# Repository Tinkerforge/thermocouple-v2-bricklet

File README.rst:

Thermocouple Bricklet 2.0
=========================

This repository contains the firmware source code and the hardware design
files. The documentation generator configs can be found at
https://github.com/Tinkerforge/generators

Repository Content
------------------

software/:
 * examples/: Examples for all supported languages
 * build/: Compiled files
 * src/: Source code of firmware
 * Makefile: Makefile to build project

hardware/:
 * Contains KiCad project files and additionally schematics as PDF

datasheets/:
 * Contains datasheets for sensors and complex ICs that are used

Hardware
--------

The hardware is designed with the open source EDA Suite KiCad
(http://www.kicad.org). Before you are able to open the files,
you have to install the Tinkerforge kicad-libraries
(https://github.com/Tinkerforge/kicad-libraries). You can either clone
them directly in hardware/ or clone them in a separate folder and
symlink them into hardware/
(ln -s kicad_path/kicad-libraries project_path/hardware). After that you
can open the .pro file in hardware/ with KiCad and from there view and
modify the schematics and the PCB layout.

Software
--------

If you want to do your own Brick/Bricklet firmware development we highly
recommend that you use our build environment setup script and read the
tutorial (https://www.tinkerforge.com/en/doc/Tutorials/Tutorial_Build_Environment/Tutorial.html).

To compile the C code we recommend you to install the newest GNU Arm Embedded
Toolchain (https://launchpad.net/gcc-arm-embedded/+download).
You also need to install bricklib2 (https://github.com/Tinkerforge/bricklib2).

You can either clone it directly in software/src/ or clone it in a
separate folder and symlink it into software/src/
(ln -s bricklib_path/bricklib2 project_path/software/src/). Finally make sure to
have CMake installed (http://www.cmake.org/cmake/resources/software.html).

After that you can build the firmware by invoking make in software/.
The firmware (.zbin) can then be found in software/build/ and uploaded
with brickv (click button "Flashing" on start screen).

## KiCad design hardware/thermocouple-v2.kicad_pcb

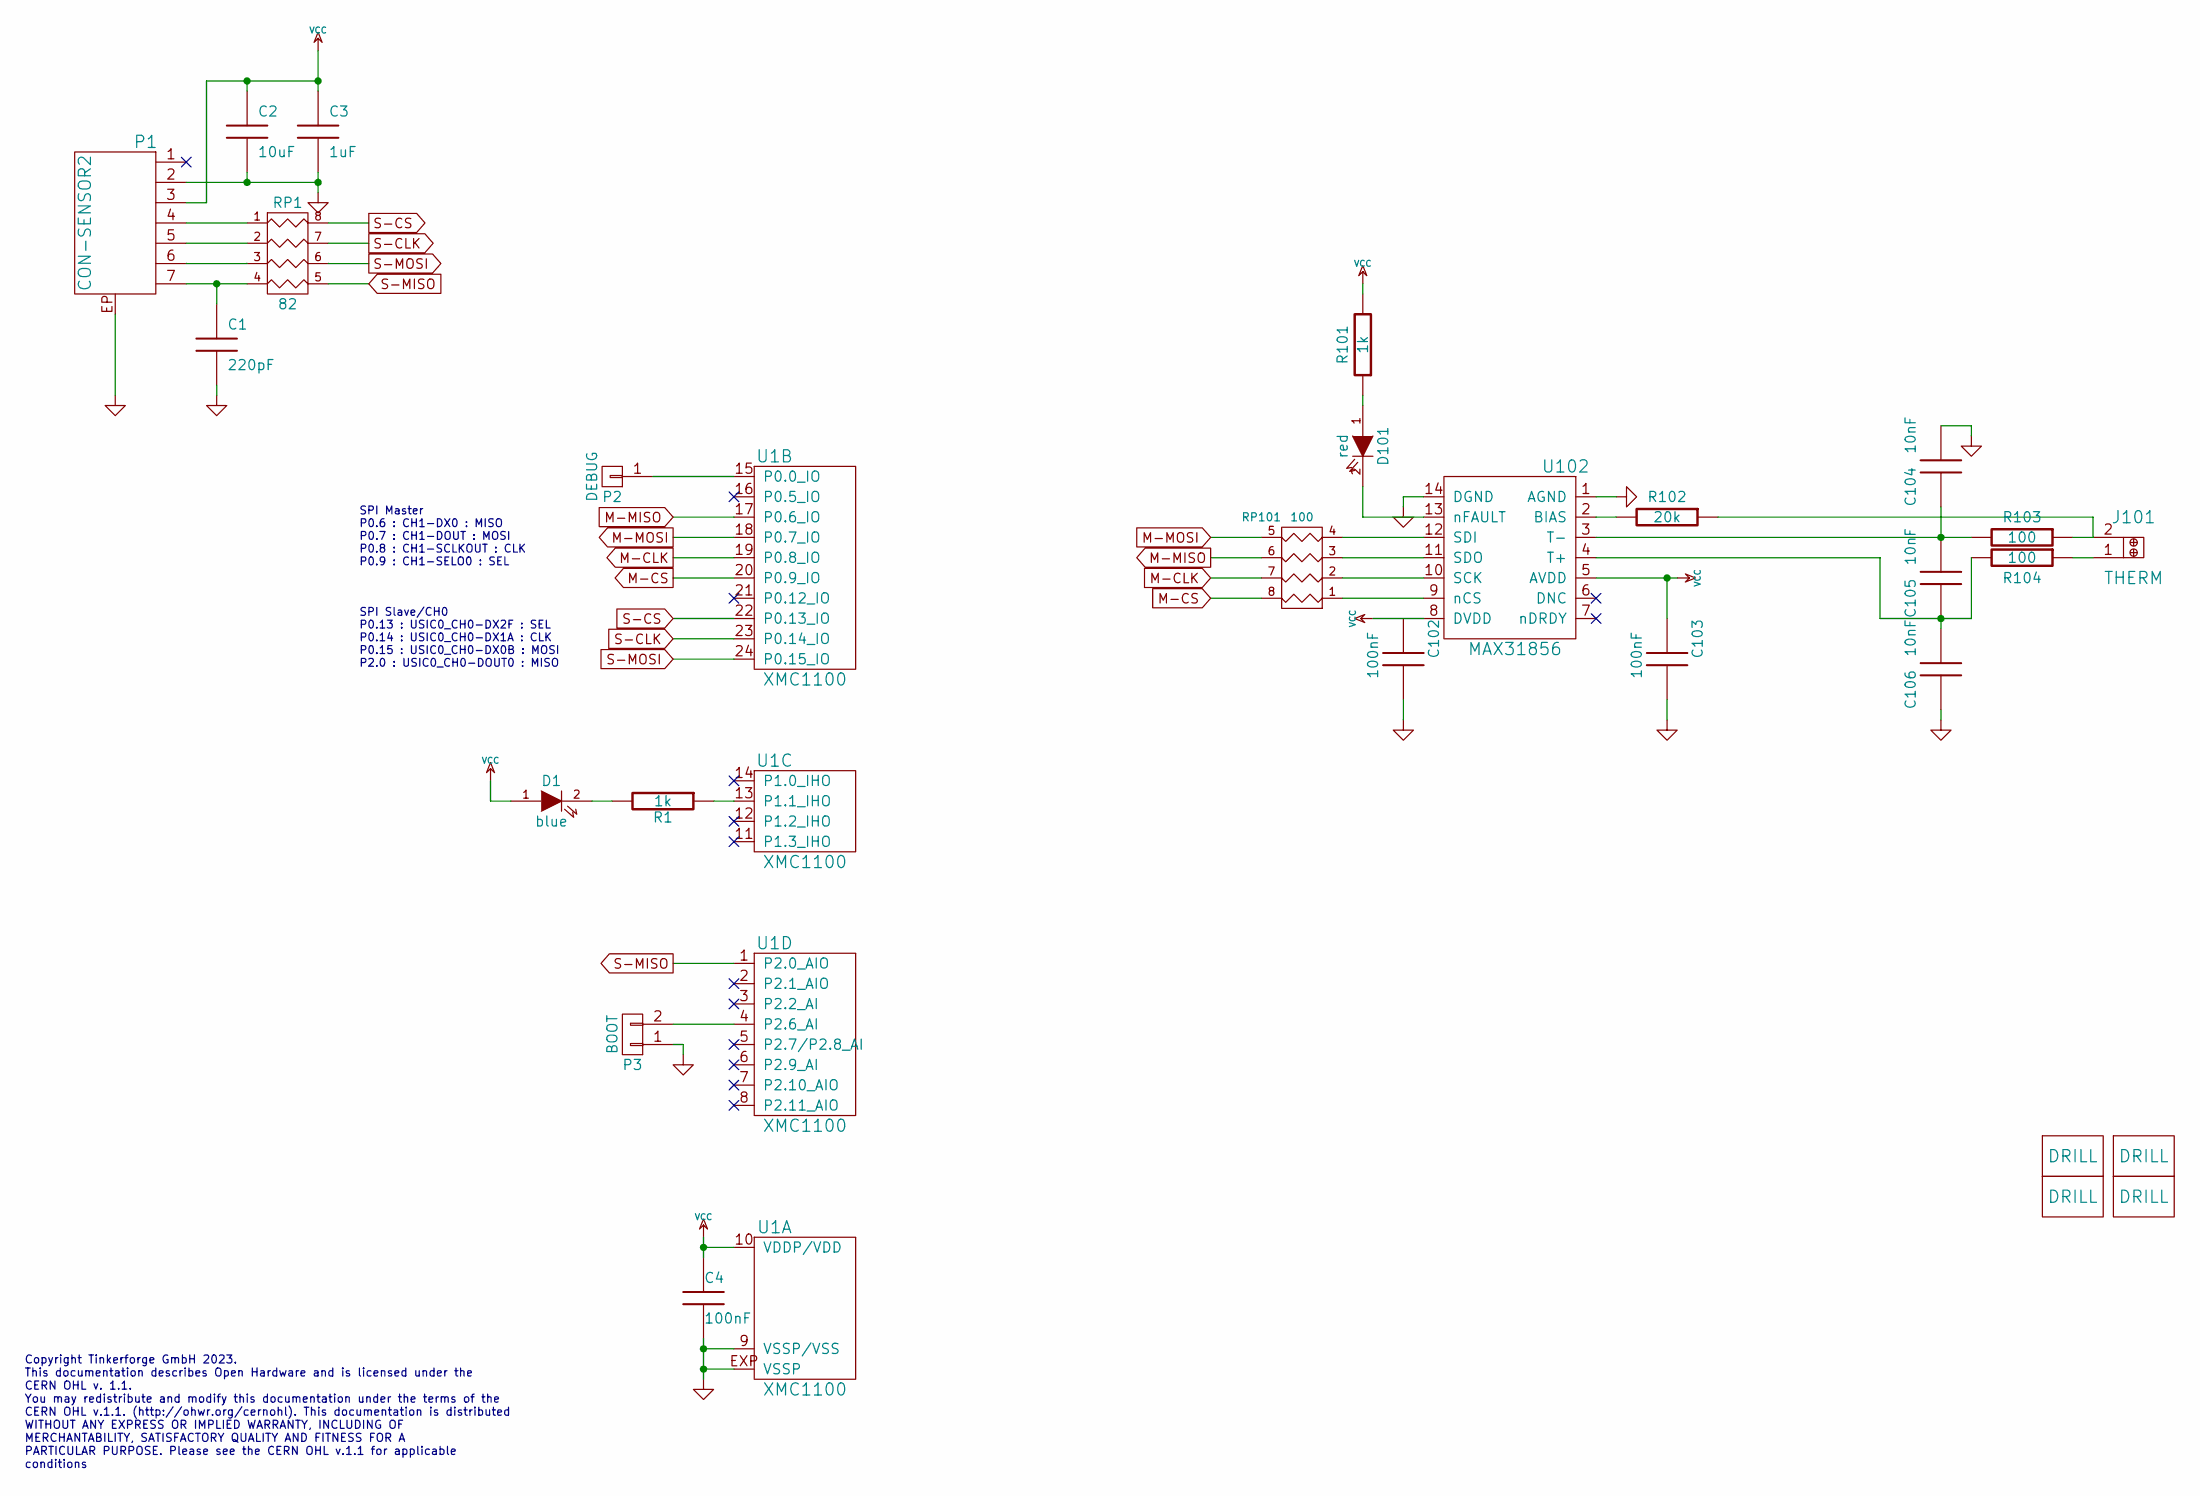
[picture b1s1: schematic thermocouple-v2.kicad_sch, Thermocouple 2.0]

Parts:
C1: 220pF; C0402F
C2: 10uF; C0805
C3: 1uF; C0603F
C4, C102, C103: 100nF; C0603F
C104, C105, C106: 10nF; C0603F
D1: blue; D0603F
D101: red; D0603F
J101: THERM; PCC_SMP
P1: CON-SENSOR2
P2: DEBUG; DEBUG_PAD
P3: BOOT; SolderJumper
R1, R101: 1k; R0603F
R102: 20k; R1206
R103, R104: 100; R1206
RP1: 82; 4X0402
RP101: 100; 0603X4
U1: XMC1100; QFN24-4x4mm-0.5mm
U102: MAX31856; TSSOP14
U103, U104, U105, U106: DRILL; DRILL_NP

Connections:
GND: C1.2, C2.2, C3.2, C4.2, C102.2, C103.2, C104.2, C106.1, P1.2, P1.EP, P3.1, U1.9 (VSSP/VSS), U1.EXP (VSSP), U102.1 (AGND), U102.14 (DGND)
M-CLK: RP101.7 (R2), U1.19 (P0.8_IO)
M-CS: RP101.8 (R1), U1.20 (P0.9_IO)
M-MISO: RP101.6 (R3), U1.17 (P0.6_IO)
M-MOSI: RP101.5 (R4), U1.18 (P0.7_IO)
unnamed: C1.1, P1.7, RP1.4
unnamed: C104.1, C105.2, R103.2, U102.3 (T-)
unnamed: C105.1, C106.2, R104.2, U102.4 (T+)
unnamed: D1.2 (K), R1.2
unnamed: D101.1 (A), R101.1
unnamed: D101.2 (K), U102.13 (nFAULT)
unnamed: J101.1, R104.1
unnamed: J101.2, R102.1, R103.1
unnamed: P1.4, RP1.1
unnamed: P1.5, RP1.2
unnamed: P1.6, RP1.3
unnamed: P2.1, U1.15 (P0.0_IO)
unnamed: P3.2, U1.4 (P2.6_AI)
unnamed: R1.1, U1.13 (P1.1_IHO)
unnamed: R102.2, U102.2 (BIAS)
unnamed: RP101.1, U102.9 (nCS)
unnamed: RP101.2, U102.10 (SCK)
unnamed: RP101.3, U102.11 (SDO)
unnamed: RP101.4, U102.12 (SDI)
S-CLK: RP1.7 (R2), U1.23 (P0.14_IO)
S-CS: RP1.8 (R1), U1.22 (P0.13_IO)
S-MISO: RP1.5 (R4), U1.1 (P2.0_AIO)
S-MOSI: RP1.6 (R3), U1.24 (P0.15_IO)
VCC: C2.1, C3.1, C4.1, C102.1, C103.1, D1.1 (A), P1.3, R101.2, U1.10 (VDDP/VDD), U102.5 (AVDD), U102.8 (DVDD)

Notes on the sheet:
Copyright Tinkerforge GmbH 2023. This documentation describes Open Hardware and is licensed under the CERN OHL v. 1.1. You may redistribute and modify this documentation under the terms of the CERN OHL v.1.1. (http://ohwr.org/cernohl). This documentation is distributed WITHOUT ANY EXPRESS OR IMPLIE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
SPI Slave/CH0 P0.13 : USIC0_CH0-DX2F : SEL P0.14 : USIC0_CH0-DX1A : CLK P0.15 : USIC0_CH0-DX0B : MOSI P2.0 : USIC0_CH0-DOUT0 : MISO
SPI Master P0.6 : CH1-DX0 : MISO P0.7 : CH1-DOUT : MOSI P0.8 : CH1-SCLKOUT : CLK P0.9 : CH1-SELO0 : SEL

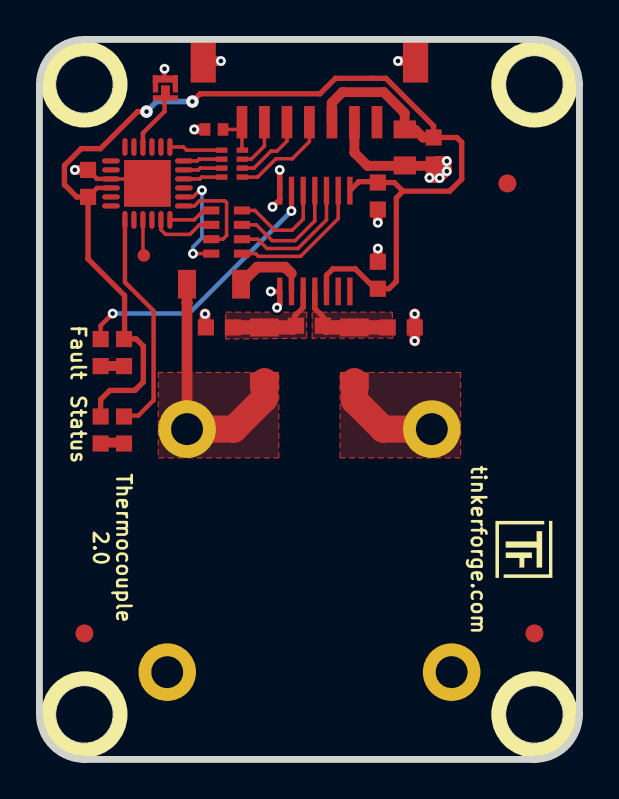
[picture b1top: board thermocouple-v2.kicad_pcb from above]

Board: 2 copper layers, 30.0 x 40.0 mm, 32 parts (1 on the bottom side), 29 nets.

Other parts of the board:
Fiducial_Mark: VAL**; Fiducial_Mark
Fiducial_Mark#2, Fiducial_Mark#3: VAL**; Fiducial_Mark
VAL: CE_5mm

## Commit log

2018-01-15 Add readme
2018-01-15 Add license
2018-01-15 Add datasheet
2018-01-15 Add initial schematic
2018-01-15 Change footprint
2018-01-15 Add initial pcb
2018-01-16 Move LED
2018-01-16 Add layout
2018-01-16 Minor adujustments
2018-01-16 Change VCC route to CoMCU
2018-01-16 Add CoMCU logo
2018-02-20 Add .gitignore
2018-02-20 Cleanup KiCad libraries config
    Ensure LibDir=kicad-libraries and LibName1=tinkerforge.
    Remove special library.
2018-03-08 Working firmware skeleton:
    1. Dummy set/get configuration.
    2. SPI init.
    3. Pending actual SPI transaction init implementation.
2018-03-09 SPI initialization and implementation of register write function
2018-03-12 Define RX/TX buffer length
2018-03-12 Implement SPI register read
2018-03-13 Implement set configuration function
2018-03-13 Firmware implementation
2018-03-14 Initialize default configuration in the init function
2018-03-15 Avoid defining configuration parameter types as they are already defined in communication.c, use them instead
2018-03-15 fix text size
2018-03-15 Return invalid parameter error if unknown config parameters are given
2018-03-15 fix logo positions
2018-03-27 specify processor
2018-04-23 Add 3d information
2018-04-23 Add 3d model (*.FCStd & *.step)
2018-05-04 Rename files
2018-05-04 Add schematic PDF
2018-05-28 Add examples
2018-06-06 Adapt to bricklib2 callback-value changes to fix wrong threshold min/max type
2018-06-07 Update changelog for initial release
2018-06-11 Fix 3d model
2018-06-18 Change capacitor footprint(s) to C0402F
2018-06-28 Fix readme
2018-07-11 Add Makefile with docker support
2018-07-11 Update directory structure and build instructions
2018-07-11 Remove obsolete generate_makefile scripts
2018-10-04 Increase version for new release (changes in bricklib2)
2018-10-04 Add rev to changelog
2018-11-06 Add rust examples
2018-11-07 rust: Accept host names for ip connection, fix naming inconsistencies
2018-11-07 rust: Rename callback receivers.
2018-12-14 Add go examples.
2018-12-14 go: Fix printf parameters.
2018-12-18 go: Change import path.
2018-12-18 go: Change import path again.
2018-12-20 rust: Reformat examples.
2019-01-24 mqtt: Add examples.
2019-01-24 mqtt: Fix example header.
2019-01-24 mqtt: Remove executable bit in example permissions.
2019-01-24 go: Minor example fixes.
2019-01-24 mqtt: Minor example fixes.
2019-03-28 mqtt: Fix whitespace.
2019-08-22 c: Adapt to bindings changes
2020-01-13 examples: Use python3 input instead of python2 raw_input.
2020-01-13 examples: mqtt: Remove trailing whitespace.
2020-08-19 Add uc examples.
2020-08-25 uc: Fix whitespace
2020-08-27 uc: Fix warnings.
2020-09-02 uc: Add example driver note.
2020-10-16 uc: Fix divisor type.
2021-10-25 Update KiCad link
    https://www.kicad.org/blog/2021/10/Avoid-links-to-former-kicad-domain/
2022-04-19 examples: uc: Rename TF_HalContext to TF_HAL.
2022-04-27 uc: Adapt to bindings changes
2022-07-06 Add license files.
2023-01-27 fix schematic
2023-01-27 fix pro file
2023-01-27 Data Cleanup
2025-10-04 Fix compatibility with new Docker build image (GCC 14.2.1)

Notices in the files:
hardware/thermocouple-v2.kicad_pcb:
Licensed under CERN OHL v.1.1
Copyright (©) 2023, T.Schneidermann
